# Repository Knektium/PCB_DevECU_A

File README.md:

Wolley DevECU A
===============

This is the KiCad project for the PCB for the Wolley development ECU, DevECU A.

It has an Infineon XMC1404 MCU with buffered and ESD protected GPIO.

Specifications
--------------

| Name              | Value |
| ----------------- | ----- |
| PCB layers        | 2     |
| Control Interface | CAN   |

Key Components
--------------

| Component | Part | Details |
| ----------| ---- | --------|
| MCU | Infineon XMC1404_F064X200A | ARM Cortex-M0, 32-bit, 48 MHz, 200 kB flash |
| CAN transceiver | Infineon TLE7251VSJ | |

Licence
-------

Licenced under the CERN Open Hardware Licence v1.2.

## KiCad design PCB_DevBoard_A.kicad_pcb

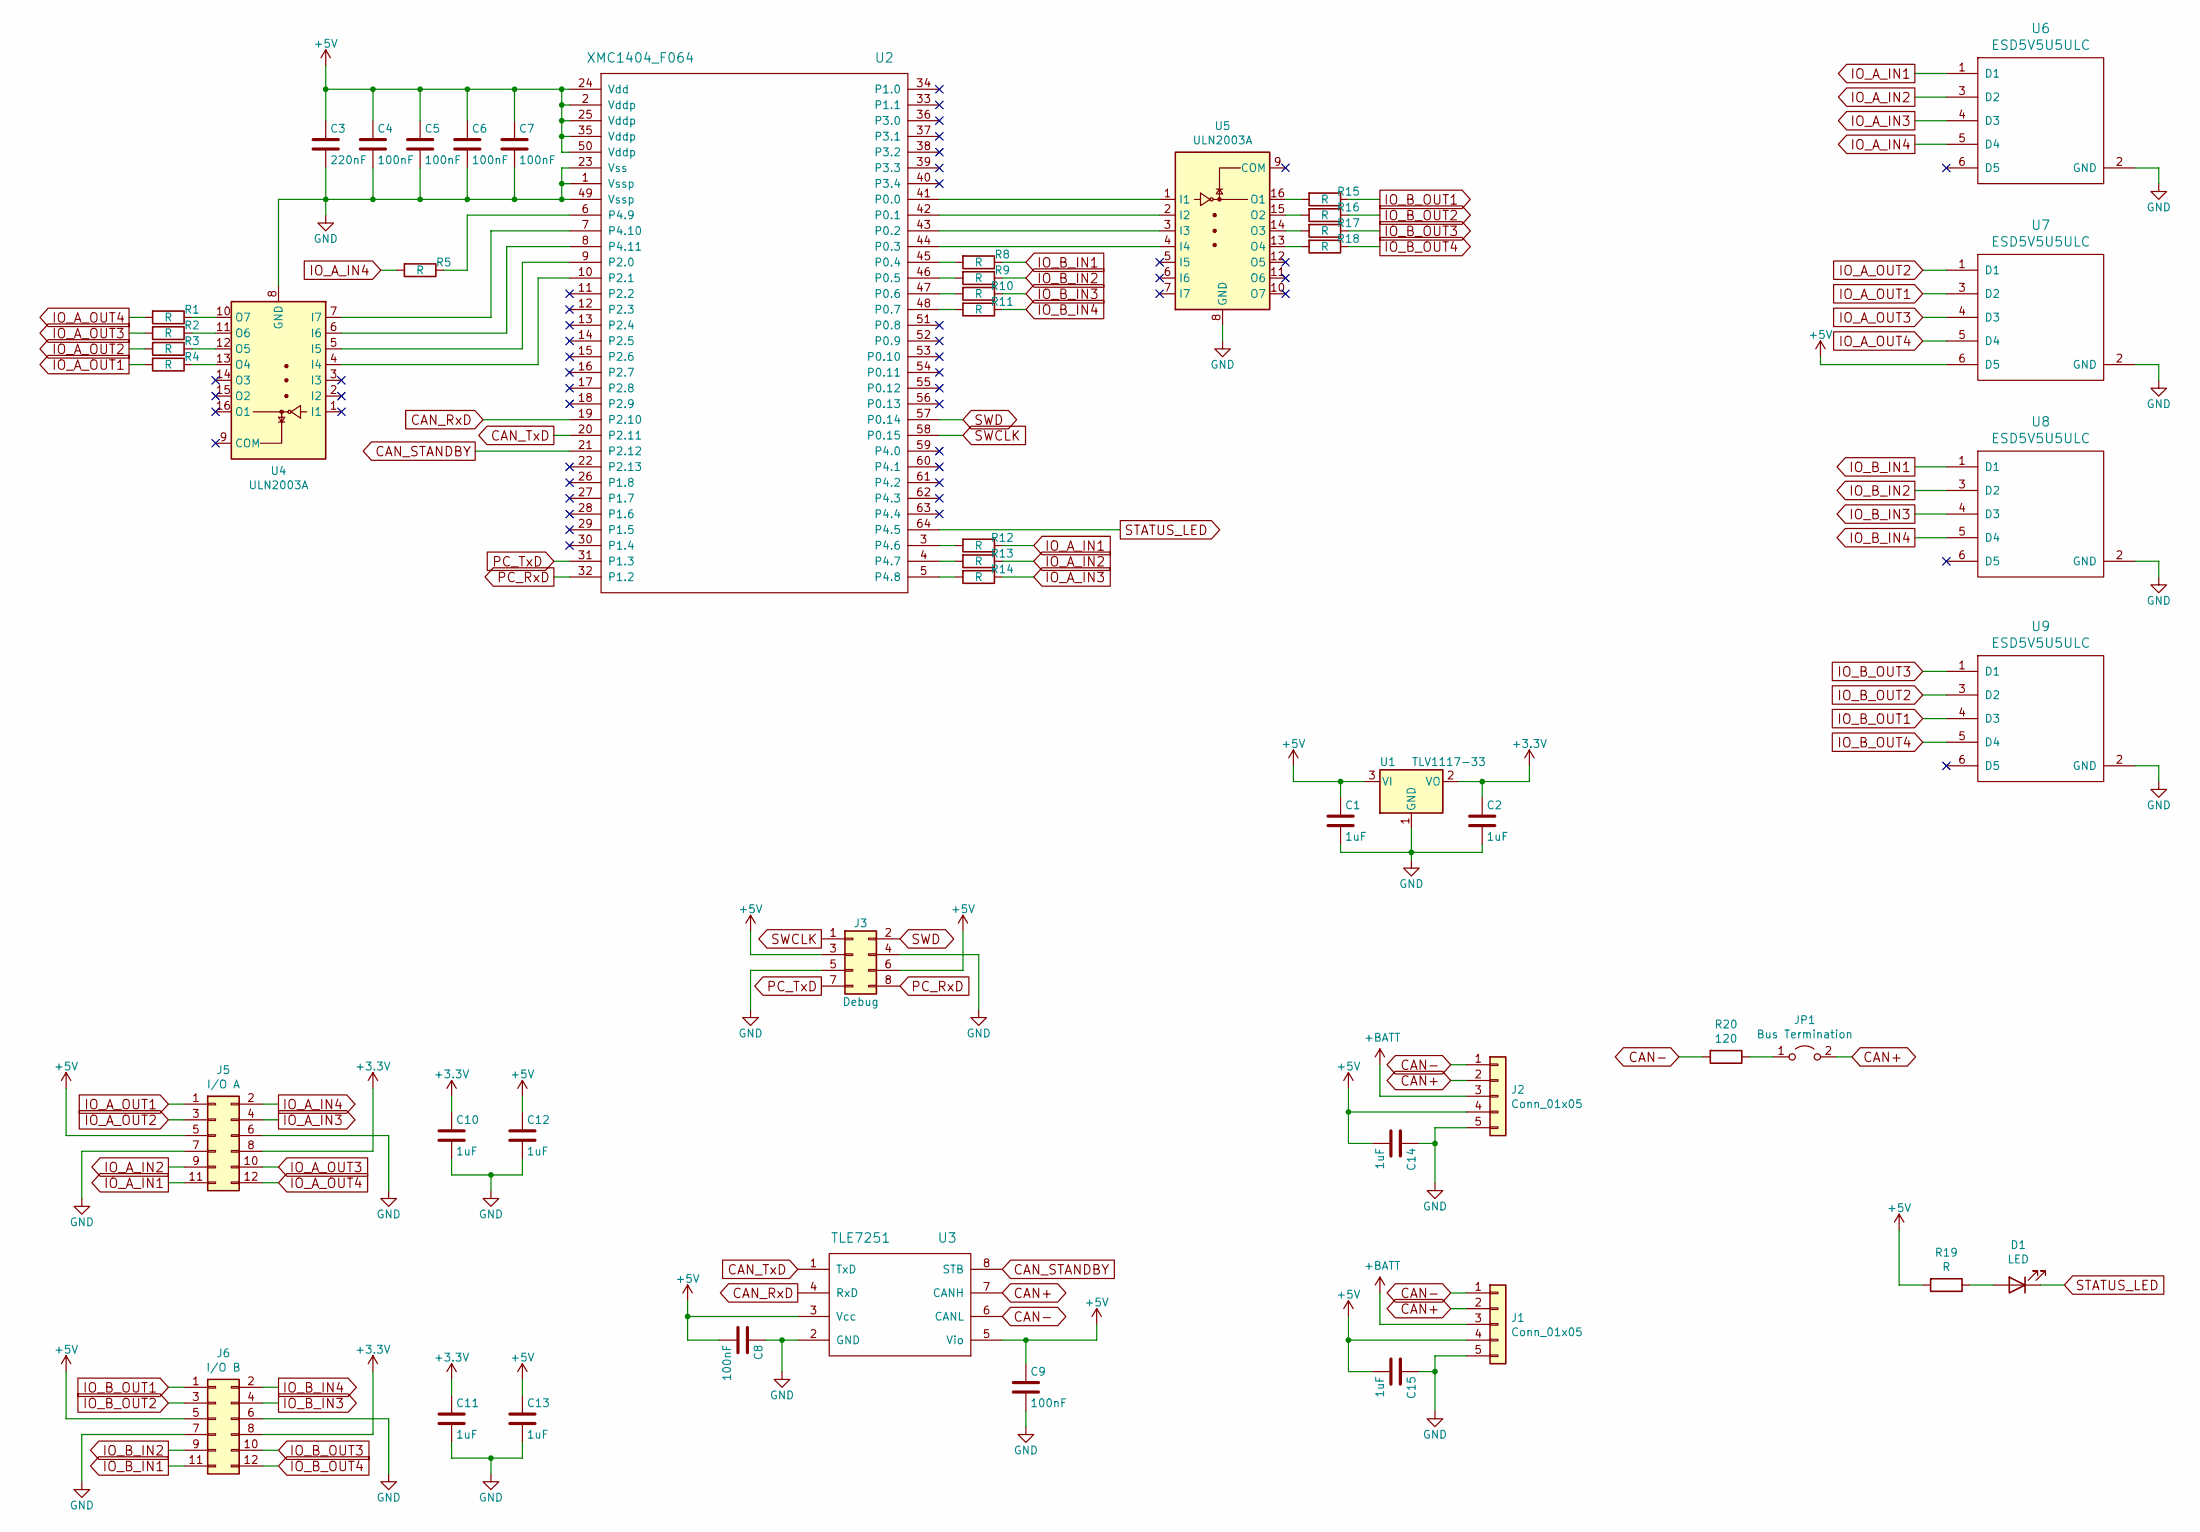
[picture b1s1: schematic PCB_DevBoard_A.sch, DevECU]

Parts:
C1, C2, C10, C11, C12, C13, C14: 1uF; C_0805_HandSoldering
C3: 220nF; C_0805_HandSoldering
C4, C5, C6, C7, C8, C9: 100nF; C_0805_HandSoldering
C15: 1uF; C_0805_2012Metric_Pad1.18x1.45mm_HandSolder
D1: LED; D_0805
J1, J2: Conn_01x05; WolleyInterconnect_THT_Angeled
J3: Debug; Pin_Header_Straight_2x04_Pitch2.54mm_SMD
J5: I/O A; Pin_Header_Angled_2x06_Pitch2.54mm
J6: I/O B; Pin_Header_Angled_2x06_Pitch2.54mm
JP1: Bus Termination; PinHeader_1x02_P2.54mm_Vertical
R1, R2, R3, R4, R5, R8, R9, R10, R11, R12, R13, R14, R15, R16, R17, R18, R19: R; R_0805_HandSoldering
R20: 120; R_0805_HandSoldering
U1: TLV1117-33; SOT-223-3_TabPin2
U2: XMC1404_F064; TQFP-64_10x10mm_Pitch0.5mm_Handsoldering
U3: TLE7251; SOIC-8_3.9x4.9mm_Pitch1.27mm
U4, U5: ULN2003A; SOIC-16_3.9x9.9mm_Pitch1.27mm
U6, U7, U8, U9: ESD5V5U5ULC; TSOP-6_1.65x3.05mm_Pitch0.95mm

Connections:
+3V3: C2.1, C10.1, C11.1, J5.8, J6.8, U1.2 (VO)
+BATT: J1.3, J2.3
CAN+: J1.2, J2.2, JP1.2 (B), U3.7 (CANH)
CAN-: J1.1, J2.1, R20.2, U3.6 (CANL)
CAN_RxD: U2.19 (P2.10), U3.4 (RxD)
CAN_STANDBY: U2.21 (P2.12), U3.8 (STB)
CAN_TxD: U2.20 (P2.11), U3.1 (TxD)
IO_A_IN1: J5.11, R12.1, U6.1 (D1)
IO_A_IN2: J5.9, R13.1, U6.3 (D2)
IO_A_IN3: J5.4, R14.1, U6.4 (D3)
IO_A_IN4: J5.2, R5.2, U6.5 (D4)
IO_A_OUT1: J5.1, R4.2, U7.3 (D2)
IO_A_OUT2: J5.3, R3.2, U7.1 (D1)
IO_A_OUT3: J5.10, R2.2, U7.4 (D3)
IO_A_OUT4: J5.12, R1.2, U7.5 (D4)
IO_B_IN1: J6.11, R8.1, U8.1 (D1)
IO_B_IN2: J6.9, R9.1, U8.3 (D2)
IO_B_IN3: J6.4, R10.1, U8.4 (D3)
IO_B_IN4: J6.2, R11.1, U8.5 (D4)
IO_B_OUT1: J6.1, R15.1, U9.4 (D3)
IO_B_OUT2: J6.3, R16.1, U9.3 (D2)
IO_B_OUT3: J6.10, R17.1, U9.1 (D1)
IO_B_OUT4: J6.12, R18.1, U9.5 (D4)
unnamed: D1.2 (A), R19.1
unnamed: JP1.1 (A), R20.1
unnamed: R1.1, U4.10 (O7)
unnamed: R2.1, U4.11 (O6)
unnamed: R3.1, U4.12 (O5)
unnamed: R4.1, U4.13 (O4)
unnamed: R5.1, U2.6 (P4.9)
unnamed: R8.2, U2.45 (P0.4)
unnamed: R9.2, U2.46 (P0.5)
unnamed: R10.2, U2.47 (P0.6)
unnamed: R11.2, U2.48 (P0.7)
unnamed: R12.2, U2.3 (P4.6)
unnamed: R13.2, U2.4 (P4.7)
unnamed: R14.2, U2.5 (P4.8)
unnamed: R15.2, U5.16 (O1)
unnamed: R16.2, U5.15 (O2)
unnamed: R17.2, U5.14 (O3)
unnamed: R18.2, U5.13 (O4)
unnamed: U2.7 (P4.10), U4.7 (I7)
unnamed: U2.8 (P4.11), U4.6 (I6)
unnamed: U2.9 (P2.0), U4.5 (I5)
unnamed: U2.10 (P2.1), U4.4 (I4)
unnamed: U2.41 (P0.0), U5.1 (I1)
unnamed: U2.42 (P0.1), U5.2 (I2)
unnamed: U2.43 (P0.2), U5.3 (I3)
unnamed: U2.44 (P0.3), U5.4 (I4)
PC_RxD: J3.8, U2.32 (P1.2)
PC_TxD: J3.7, U2.31 (P1.3)
STATUS_LED: D1.1 (K), U2.64 (P4.5)
SWCLK: J3.1, U2.58 (P0.15)
SWD: J3.2, U2.57 (P0.14)

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
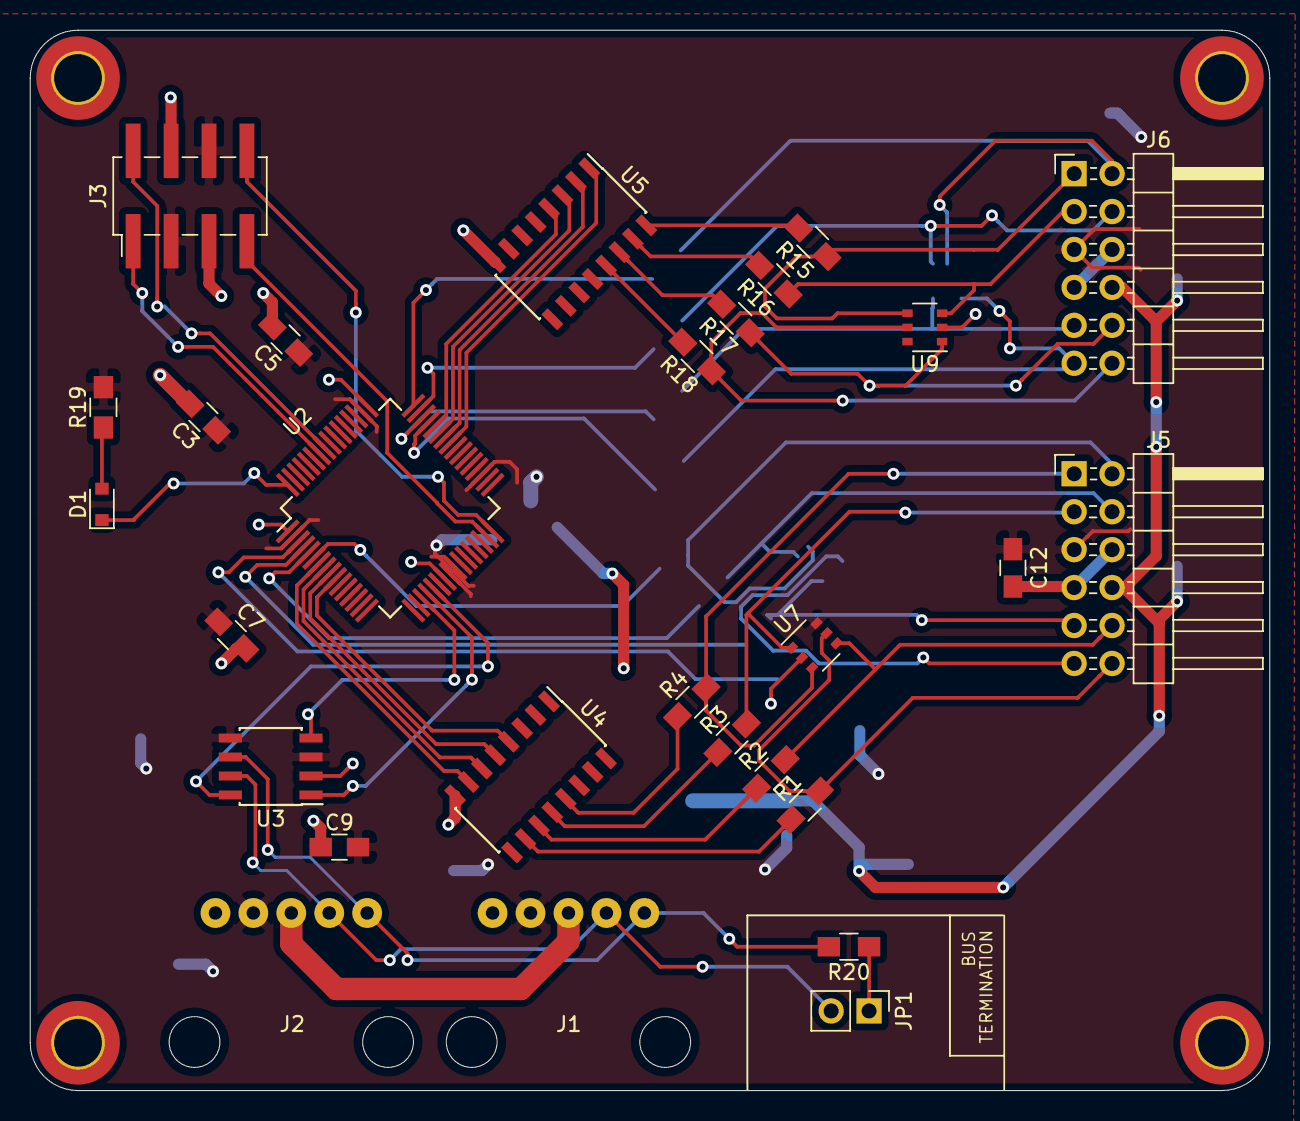
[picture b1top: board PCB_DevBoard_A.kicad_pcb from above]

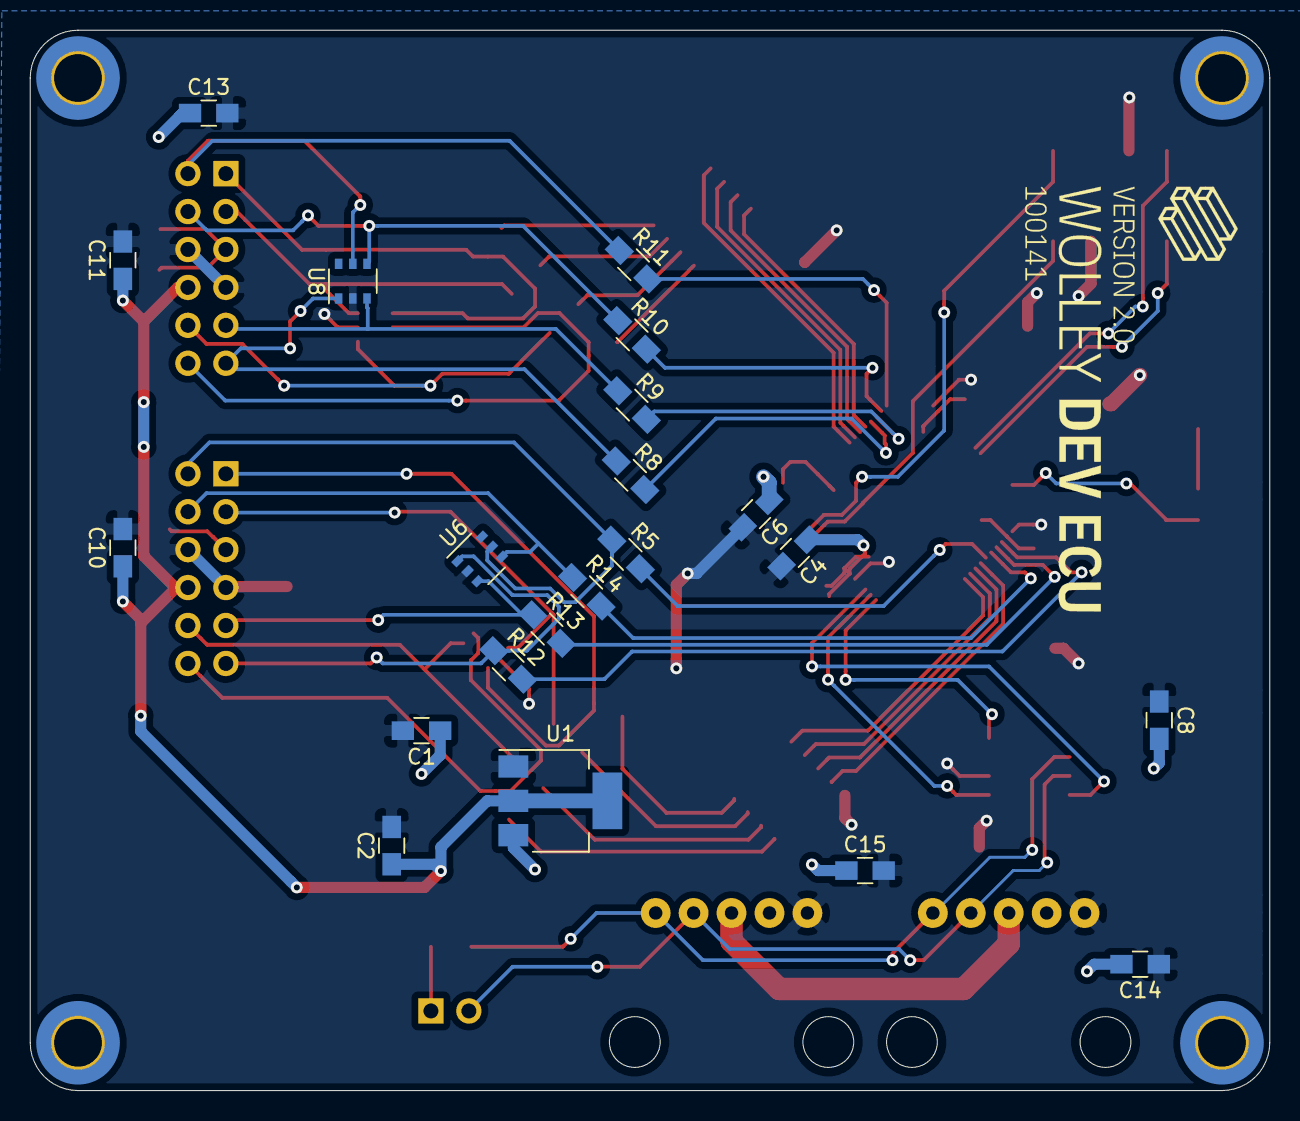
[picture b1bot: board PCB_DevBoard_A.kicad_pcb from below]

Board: 2 copper layers, 83.0 x 71.0 mm, 49 parts (21 on the bottom side), 56 nets.

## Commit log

2021-08-10 Add files
2021-08-19 Add README file
2023-03-05 Rescue
2023-03-05 Change the Wolley connectors to the new 5-pin one
2023-03-05 Replace the termination switch with a jumper
2023-05-06 Move some capacitors to a better location
2023-05-06 Improve the tracks between the connectors
2023-05-06 Remove the ground vias around the edges
2023-05-06 Update logotypes etc.
2023-05-06 Replace the M2.5 mounting holes with M3 holes
2023-05-09 Update document info
